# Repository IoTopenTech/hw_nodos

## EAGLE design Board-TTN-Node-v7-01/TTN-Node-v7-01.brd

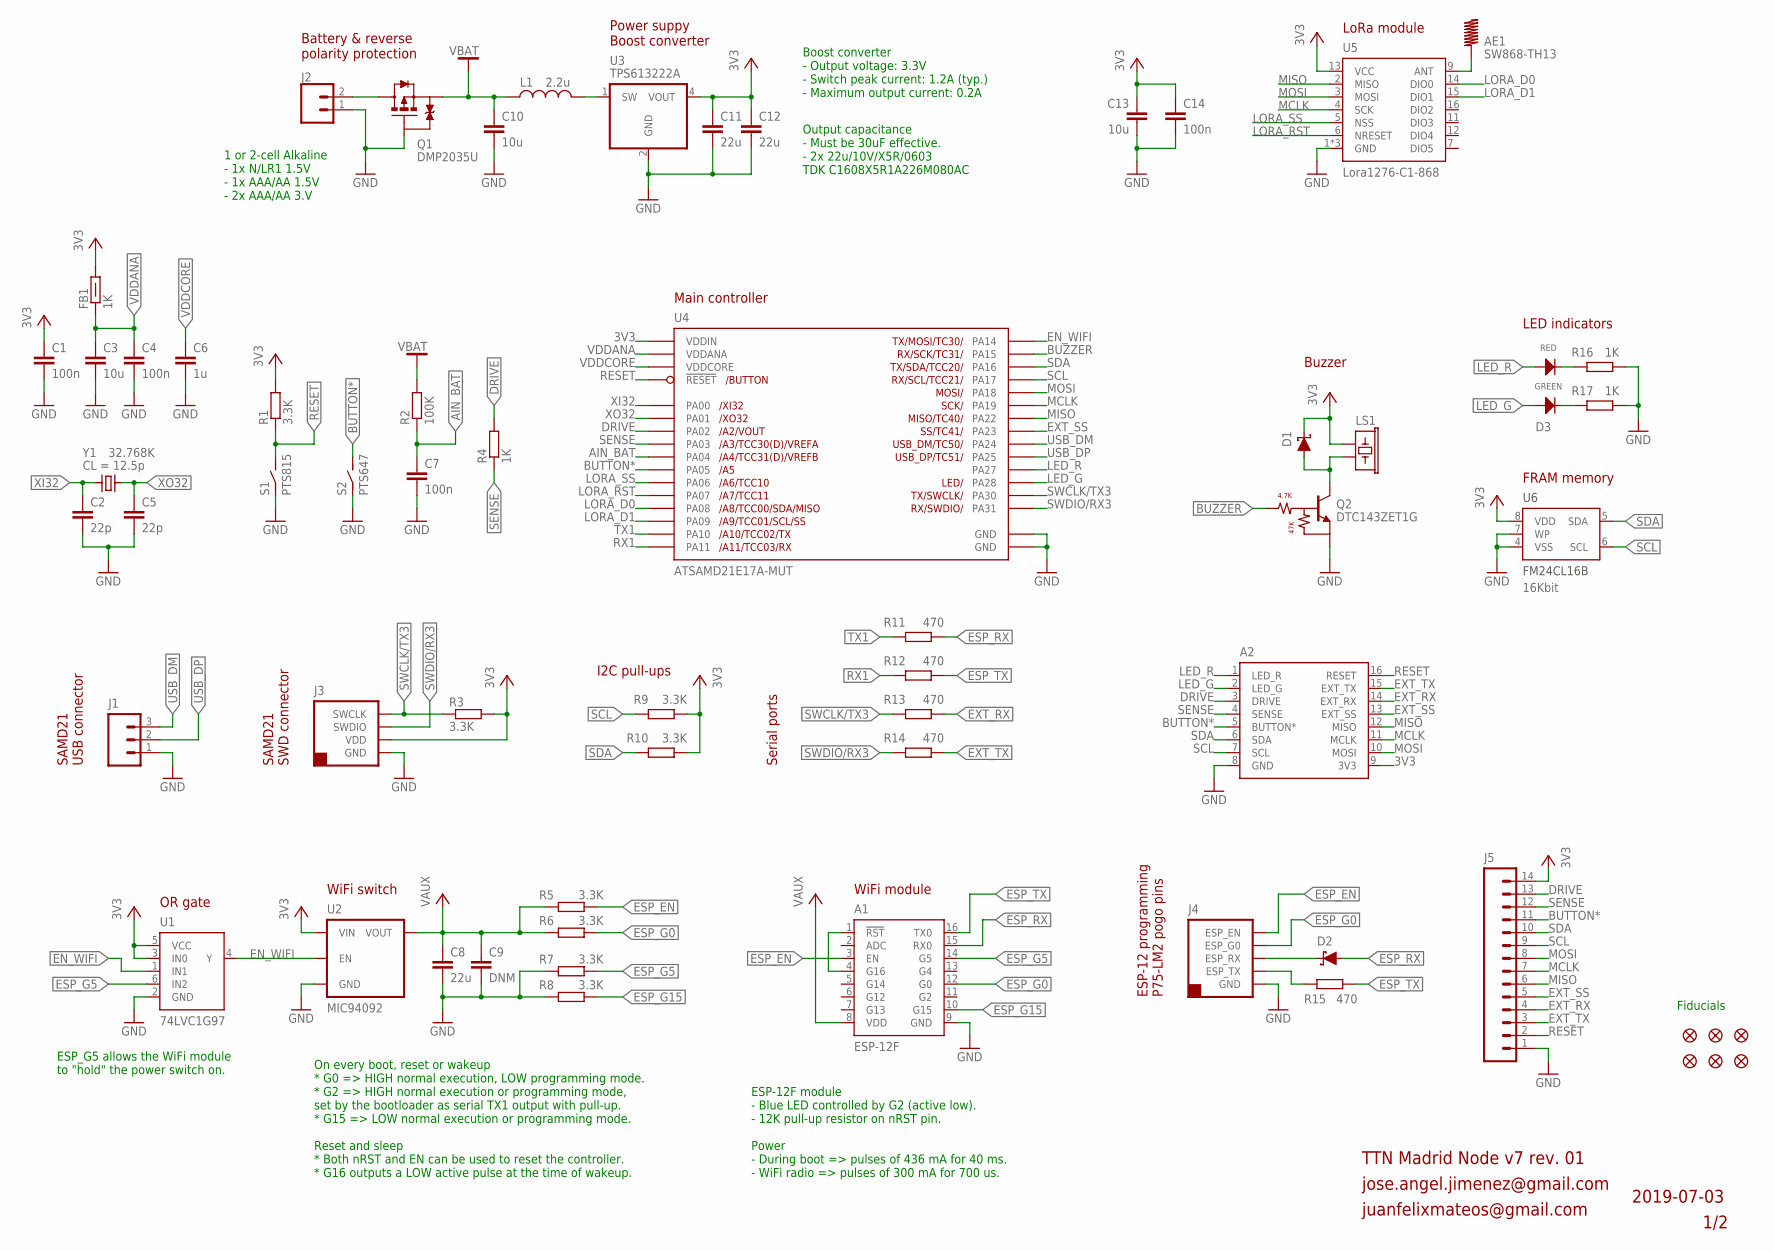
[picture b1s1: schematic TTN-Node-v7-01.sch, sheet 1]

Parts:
A1: ESP-12F; ESP-12
A2: TTN_MAD_NODE_V7_EXP
AE1: SW868-TH13; ANT-SW868-TH13
C1, C4, C7, C14: 100n; C0603; TOLERANCE 10%; VOLTAGE 50V; MPN CC0603KRX7R9BB104
C2, C5: 22p; C0603; TOLERANCE 5%; VOLTAGE 50V; MPN 06035A220JAT2A
C3, C10, C13: 10u; C0603; TOLERANCE 10%; VOLTAGE 6.3V; MPN GRM188R60J106KE47D
C6: 1u; C0603; TOLERANCE 10%; VOLTAGE 25V; MPN CC0603KRX5R8BB105
C8, C11, C12: 22u; C0603; TOLERANCE 20%; VOLTAGE 10V; MPN C1608X5R1A226M080AC
C9: DNM; C0603; TOLERANCE 20%; VOLTAGE 10V; MPN C1608X5R1A226M080AC
D1, D2: RB521S30; SOD523
D3: LTST-E682KRKGWT; LED-PLCC-4-3522
FB1: 1K; L0603
FD1, FD2, FD3, FD4, FD5, FD6: FIDUCIAL1X2; FIDUCIAL-1X2
J1: USB; 1X03
J2: CONN_02; 1X02
J3: CON-SWD-HDR-1X4-254; HDR-1X4-254-SWD
J4: CON-ESP-HDR-1X5-254; HDR-1X5-254-ESP
J5: CONN_14; 1X14
L1: 2.2u; L2520_MM; MPN SRN2512-2R2M
LS1: BUZZER-SMD-4030_MM; BUZZER-4030_MM
Q1: DMP2035U; SOT23-3
Q2: DTC143ZET1G; SC75-3
R1, R3, R9, R10: 3.3K; R0603; TOLERANCE 1%
R2: 100K; R0603; TOLERANCE 1%
R4: 1K; R0603; TOLERANCE 1%
R5, R6, R7, R8: 3.3K; R0603
R11, R12, R13, R14: 470; R0603; TOLERANCE 1%
R15: 470; R0603
R16, R17: 1K; R0603
S1: PTS815; SW-SMD-PTS815-4232
S2: PTS647; SW-SMD-PTS647-4545
U1: 74LVC1G97; SC70-6
U2: MIC94092; SOT363
U3: TPS613222A; SOT23-5
U4: ATSAMD21E17A-MUT; VQFN32L-05-5050_MM-SEGMENTED
U5: Lora1276-C1-868; RFM95W
U6: FM24CL16B; SO8
Y1: 32.768K; CRYSTAL-3215; MPN FC-135 32.7680KA-A3

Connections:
3V3: A2.9 (3V3), C1.P$1 (1), C11.P$1 (1), C12.P$1 (1), C13.P$1 (1), C14.P$1 (1), D1.C, FB1.P$2 (2), J3.2 (VDD), J5.14, LS1.1, R1.P$2 (2), R3.P$2 (2), R9.P$2 (2), R10.P$2 (2), U1.3 (IN0), U1.5 (VCC), U2.4 (VIN), U3.4 (VOUT), U4.30 (VDDIN), U5.13 (VCC), U6.8 (VDD); also elsewhere on the board
*ESP_RST: A1.1 (!RST), A1.4 (G16)
AIN_BAT: C7.P$1 (1), R2.P$1 (1), U4.5 (PA04)
ANT: AE1.ANT, U5.9 (ANT)
BOOST_SW: L1.2, U3.1 (SW)
BUTTON*: A2.5 (BUTTON*), J5.11, S2.3 (2), S2.4 (2), U4.6 (PA05)
BUZZER: Q2.1 (B), U4.16 (PA15)
CG: D3.3 (C_GREEN), R17.P$1 (1)
CR: D3.1 (C_RED), R16.P$1 (1)
DRIVE: A2.3 (DRIVE), J5.13, R4.P$2 (2), U4.3 (PA02)
EN_WIFI: U1.1 (IN1), U1.4 (Y), U2.6 (EN), U4.15 (PA14)
ESP_EN: A1.3 (EN), J4.5 (ESP_EN), R5.P$2 (2)
ESP_G0: A1.12 (G0), J4.4 (ESP_G0), R6.P$2 (2)
ESP_G5: A1.14 (G5), R7.P$2 (2), U1.6 (IN2)
ESP_G15: A1.10 (G15), R8.P$2 (2)
ESP_RX: A1.15 (RX0), D2.A, R11.P$2 (2)
ESP_RX_CON: D2.C, J4.3 (ESP_RX)
ESP_TX: A1.16 (TX0), R12.P$2 (2), R15.P$2 (2)
ESP_TX_CON: J4.2 (ESP_TX), R15.P$1 (1)
EXT_RX: A2.14 (EXT_RX), J5.4, R13.P$2 (2)
EXT_SS: A2.13 (EXT_SS), J5.5, U4.22 (PA23)
EXT_TX: A2.15 (EXT_TX), J5.3, R14.P$2 (2)
GND: A1.9 (GND), A2.8 (GND), C1.P$2 (2), C2.P$2 (2), C3.P$2 (2), C4.P$2 (2), C5.P$2 (2), C6.P$2 (2), C7.P$2 (2), C8.P$2 (2), C9.P$2 (2), C10.P$2 (2), C11.P$2 (2), C12.P$2 (2), C13.P$2 (2), C14.P$2 (2), J1.1, J2.1, J3.1 (GND), J4.1 (GND), J5.1, Q1.1 (G), Q2.2 (E), R7.P$1 (1), R8.P$1 (1), R16.P$2 (2), R17.P$2 (2), S1.1, S1.2 (1), S2.1, S2.2 (1), U1.2 (GND), U2.2 (GND), U2.5 (GND), U3.2 (GND), U4.10 (GND), U4.28 (GND), U4.33 (GND), U5.1 (GND), U5.8 (GND), U5.10 (GND), U6.4 (VSS), U6.7 (WP); also elsewhere on the board
LED_G: A2.2 (LED_G), D3.2 (A_GREEN), U4.27 (PA28)
LED_R: A2.1 (LED_R), D3.4 (A_RED), U4.25 (PA27)
LORA_D0: U4.11 (PA08), U5.14 (DIO0)
LORA_D1: U4.12 (PA09), U5.15 (DIO1)
LORA_RST: U4.8 (PA07), U5.6 (NRESET)
LORA_SS: U4.7 (PA06), U5.5 (NSS)
MCLK: A2.11 (MCLK), J5.7, U4.20 (PA19), U5.4 (SCK)
MISO: A2.12 (MISO), J5.6, U4.21 (PA22), U5.2 (MISO)
MOSI: A2.10 (MOSI), J5.8, U4.19 (PA18), U5.3 (MOSI)
unnamed: D1.A, LS1.2, Q2.3 (C)
RESET: A2.16 (RESET), J5.2, R1.P$1 (1), S1.3 (2), S1.4 (2), U4.26 (!RESET)
RX1: R12.P$1 (1), U4.14 (PA11)
SCL: A2.7 (SCL), J5.9, R9.P$1 (1), U4.18 (PA17), U6.6 (SCL); also elsewhere on the board
SDA: A2.6 (SDA), J5.10, R10.P$1 (1), U4.17 (PA16), U6.5 (SDA); also elsewhere on the board
SENSE: A2.4 (SENSE), J5.12, R4.P$1 (1), U4.4 (PA03)
SWCLK/TX3: J3.4 (SWCLK), R3.P$1 (1), R13.P$1 (1), U4.31 (PA30)
SWDIO/RX3: J3.3 (SWDIO), R14.P$1 (1), U4.32 (PA31); also elsewhere on the board
TX1: R11.P$1 (1), U4.13 (PA10)
USB_DM: J1.3, U4.23 (PA24)
USB_DP: J1.2, U4.24 (PA25)
VAUX: A1.8 (VDD), C8.P$1 (1), C9.P$1 (1), R5.P$1 (1), R6.P$1 (1), U2.1 (VOUT)
VBAT: C10.P$1 (1), L1.1, Q1.2 (S), R2.P$2 (2)
VDDANA: C3.P$1 (1), C4.P$1 (1), FB1.P$1 (1), U4.9 (VDDANA)
VDDCORE: C6.P$1 (1), U4.29 (VDDCORE)
VIN: J2.2, Q1.3 (D)
XI32: C2.P$1 (1), U4.1 (PA00), Y1.P$1 (1)
XO32: C5.P$1 (1), U4.2 (PA01), Y1.P$2 (2)

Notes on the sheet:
1/2
Main controller
Fiducials
2019-07-03
Power suppy Boost converter
SAMD21 SWD connector
Battery & reverse polarity protection
1 or 2-cell Alkaline - 1x N/LR1 1.5V - 1x AAA/AA 1.5V - 2x AAA/AA 3.V
Boost converter - Output voltage: 3.3V - Switch peak current: 1.2A (typ.) - Maximum output current: 0.2A
ESP-12F module - Blue LED controlled by G2 (active low). - 12K pull-up resistor on nRST pin. Power - During boot => pulses of 436 mA for 40 ms. - WiFi radio => pulses of 300 mA for 700 us.
On every boot, reset or wakeup * G0 => HIGH normal execution, LOW programming mode. * G2 => HIGH normal execution or programming mode, set by the bootloader as serial TX1 output with pull-up. * G15 => LOW normal execution or programming mode. Reset and sleep * Both nRST and EN can be used to reset 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
WiFi module
Output capacitance - Must be 30uF effective. - 2x 22u/10V/X5R/0603 TDK C1608X5R1A226M080AC
WiFi switch
FRAM memory
ESP-12 programming P75-LM2 pogo pins
LoRa module
SAMD21 USB connector
I2C pull-ups
Serial ports
LED indicators
Buzzer
OR gate
ESP_G5 allows the WiFi module to "hold" the power switch on.
TTN Madrid Node v7 rev. 01
jose.angel.jimenez@gmail.com
juanfelixmateos@gmail.com

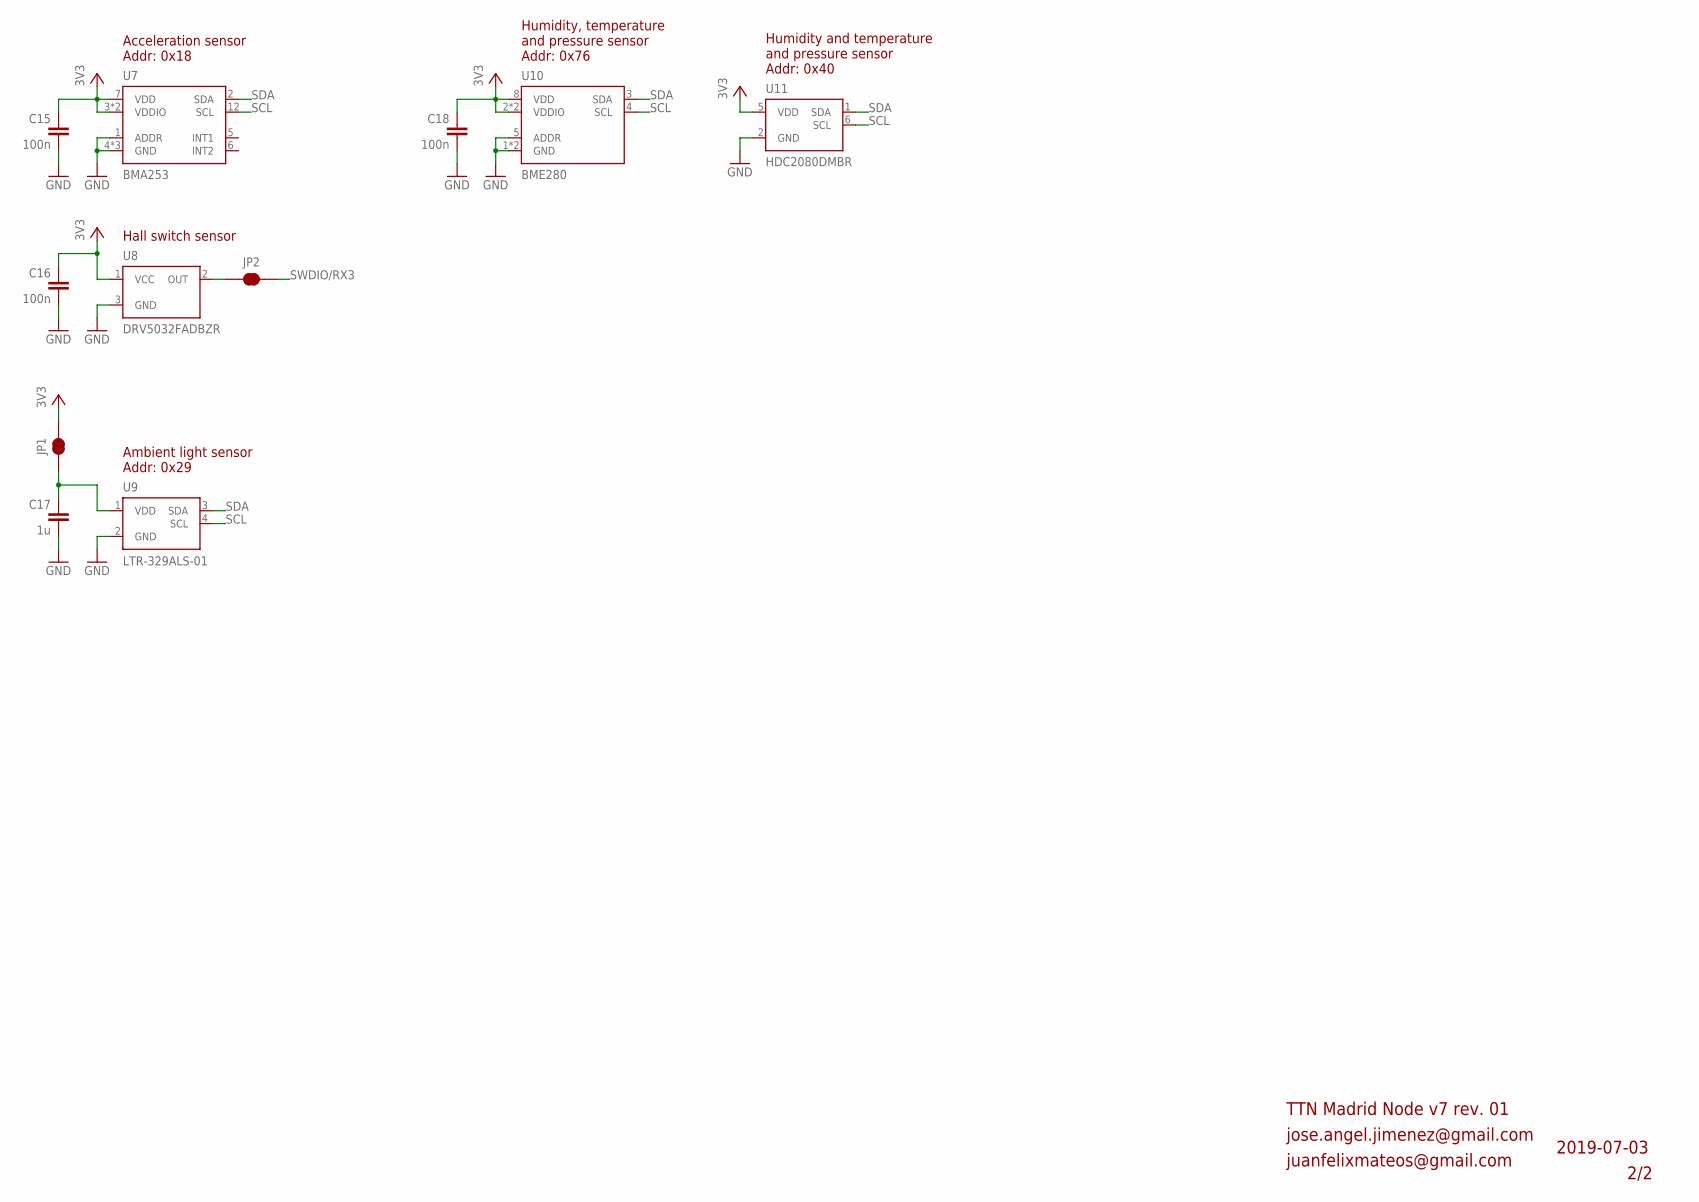
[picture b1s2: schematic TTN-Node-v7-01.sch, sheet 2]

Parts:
C15, C16, C18: 100n; C0603; TOLERANCE 10%; VOLTAGE 50V; MPN CC0603KRX7R9BB104
C17: 1u; C0603; TOLERANCE 10%; VOLTAGE 25V; MPN CC0603KRX5R8BB105
JP1, JP2: JUMPER-SMT_2_NC_TRACE-OUTLINE; SMT-JUMPER_2_NC_TRACE_OUTLINE
U7: BMA253; LGA12
U8: DRV5032FADBZR; SOT23-3
U9: LTR-329ALS-01; CHIPLED-PLCC4-2020MM
U10: BME280
U11: HDC2080DMBR; WSON-6-NOPAD

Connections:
3V3: C15.P$1 (1), C16.P$1 (1), C18.P$1 (1), JP1.2, U7.3 (VDDIO), U7.7 (VDD), U7.11 (VDDIO), U8.1 (VCC), U10.2 (VDDIO), U10.6 (VDDIO), U10.8 (VDD), U11.5 (VDD); also elsewhere on the board
GND: C15.P$2 (2), C16.P$2 (2), C17.P$2 (2), C18.P$2 (2), U7.1 (ADDR), U7.4 (GND), U7.8 (GND), U7.9 (GND), U8.3 (GND), U9.2 (GND), U10.1 (GND), U10.5 (ADDR), U10.7 (GND), U11.2 (GND); also elsewhere on the board
LTR_3V3: C17.P$1 (1), JP1.1, U9.1 (VDD)
unnamed: JP2.1, U8.2 (OUT)
SCL: U7.12 (SCL), U9.4 (SCL), U10.4 (SCL), U11.6 (SCL); also elsewhere on the board
SDA: U7.2 (SDA), U9.3 (SDA), U10.3 (SDA), U11.1 (SDA); also elsewhere on the board
SWDIO/RX3: JP2.2; also elsewhere on the board

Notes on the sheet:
2/2
2019-07-03
TTN Madrid Node v7 rev. 01
jose.angel.jimenez@gmail.com
Acceleration sensor Addr: 0x18
Humidity, temperature and pressure sensor Addr: 0x76
Hall switch sensor
Ambient light sensor Addr: 0x29
Humidity and temperature and pressure sensor Addr: 0x40
juanfelixmateos@gmail.com

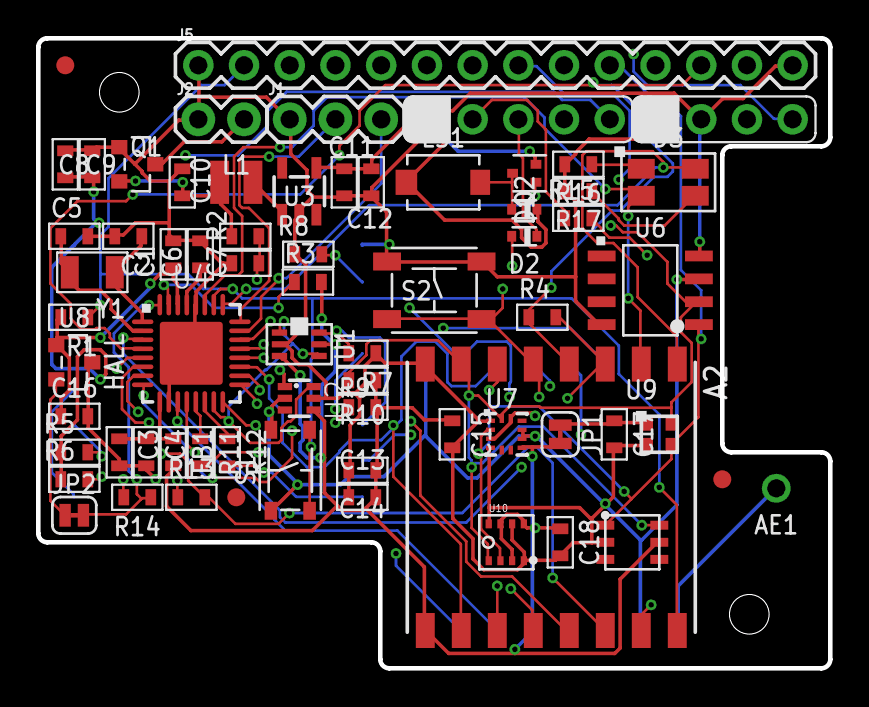
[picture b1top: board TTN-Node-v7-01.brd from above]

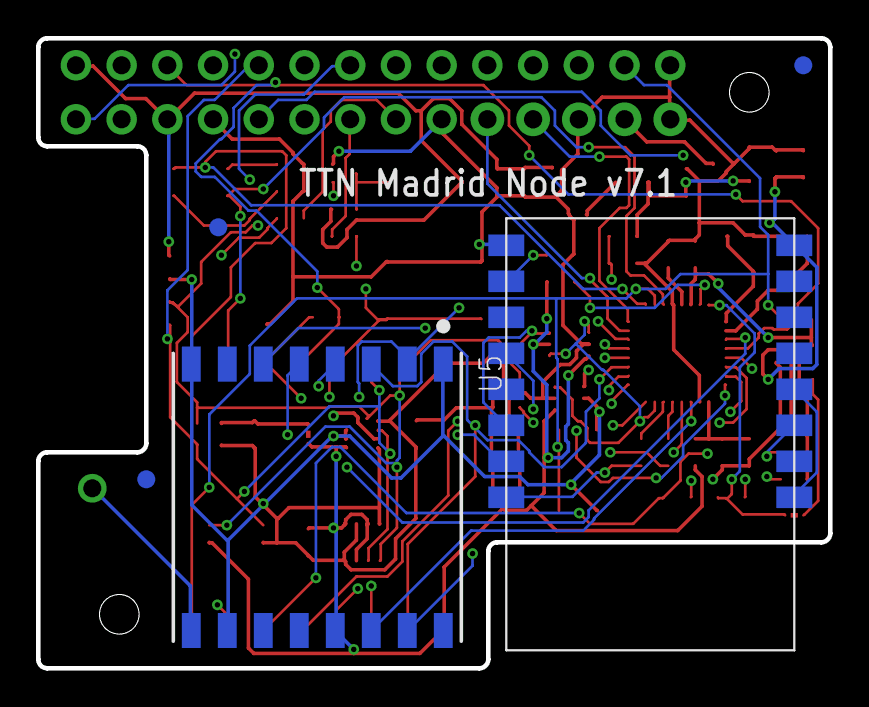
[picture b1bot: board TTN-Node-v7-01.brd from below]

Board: 4 copper layers, 44.0 x 35.0 mm, 73 parts (5 on the bottom side), 52 nets.

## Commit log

2019-07-10 Nodo TTN Madrid versión 7.1 - Commit inicial del proyecto, - Las placas se han enviado a fabricación pero todavía NO están probadas.

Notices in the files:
parts and their libraries:
SparkFun-Connectors: Licensing: Creative Commons ShareAlike 4.0 International - https://creativecommons.org/licenses/by-sa/4.0
